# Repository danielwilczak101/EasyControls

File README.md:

# EasyControls Overview:

ADD IMAGE OF CUBESAT AND FREE FLIER

### [EasyControls.org](http://easycontrols.org)
The website is used to allow users to upload their controls code and see how the spacecraft responds.

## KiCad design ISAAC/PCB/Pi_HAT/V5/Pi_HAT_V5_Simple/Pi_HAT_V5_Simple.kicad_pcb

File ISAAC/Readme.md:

# ISAAC:

<p align="center"> 
  <kbd>
    
  </kbd>
</p>

Originally part of the NASA Asteroid flyer program has been repurposed by the EPPL to allow anyone interested in controls to go online and connect with a real working device and test their own control algorithms on a live device that is connected to the global internet. The spacecraft has been refitted with new and improved wiring, updated computers and a website that allows for members to connect and upload code to.

### [EasyControls.org](http://easycontrols.org)
The website is used to allow users to upload their controls code and see how the spacecraft responds.

**AsteroidFreeFlier original purpose:**  
https://www.nasa.gov/feature/extreme-access-flyer-to-take-planetary-exploration-airborne

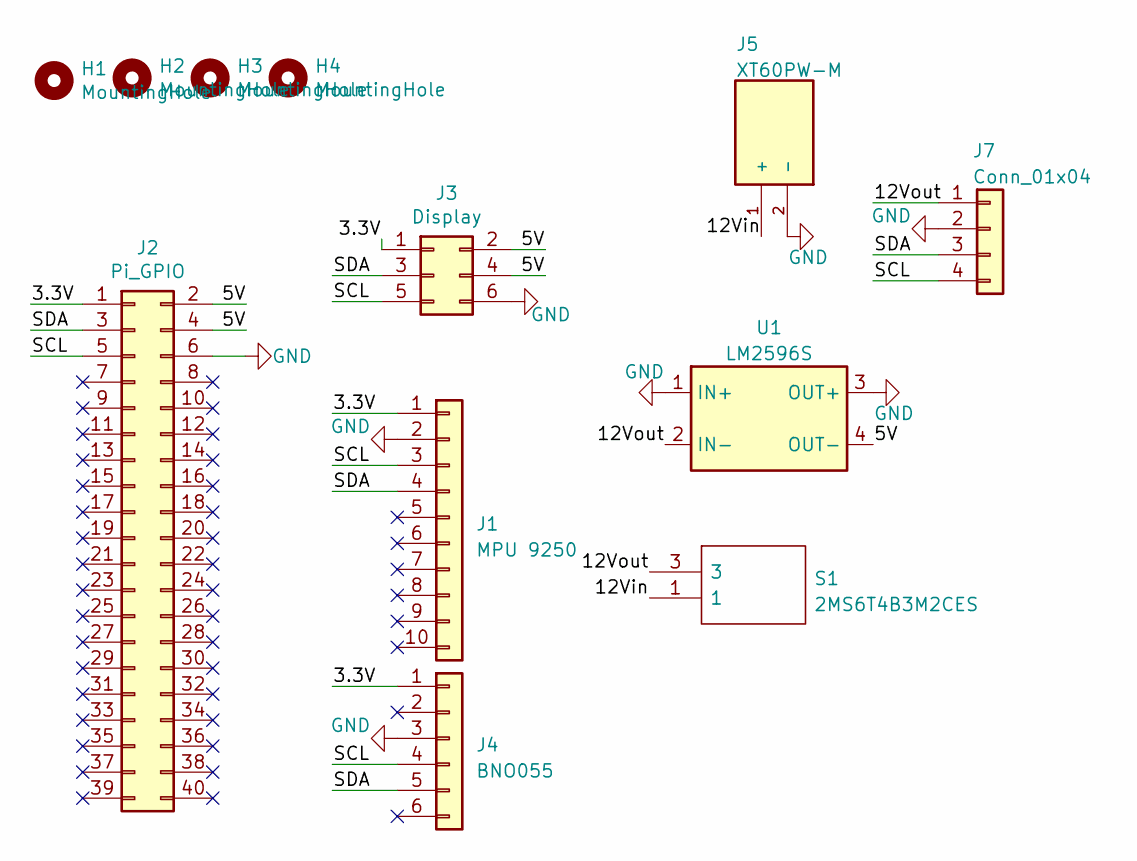
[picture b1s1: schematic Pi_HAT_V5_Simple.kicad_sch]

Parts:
H1, H2, H3, H4: MountingHole; MountingHole_2.5mm
J1: MPU 9250; PinHeader_1x10_P2.54mm_Vertical
J2: Pi_GPIO; PinHeader_2x20_P2.54mm_Vertical
J3: Display; PinHeader_2x03_P2.54mm_Vertical
J4: BNO055; PinHeader_1x06_P2.54mm_Vertical
J5: XT60PW-M; AMASS_XT60PW-M; PARTREV V1.2
J7: Conn_01x04; PinHeader_1x04_P2.54mm_Vertical
S1: 2MS6T4B3M2CES; Mouser Part Number 118-2MS6T4B3M2CES
U1: LM2596S; LM2596S_mod

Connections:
/3.3V: J1.1, J2.1, J3.1, J4.1
/5V: J2.2, J2.4, J3.2, J3.4, U1.4 (OUT-)
/12Vin: J5.1 (+), S1.1
/12Vout: J7.1, S1.3, U1.2 (IN-)
/SCL: J1.3, J2.5, J3.5, J4.4, J7.4
/SDA: J1.4, J2.3, J3.3, J4.5, J7.3
GND: J1.2, J2.6, J3.6, J4.3, J5.2 (-), J7.2, U1.1 (IN+), U1.3 (OUT+)

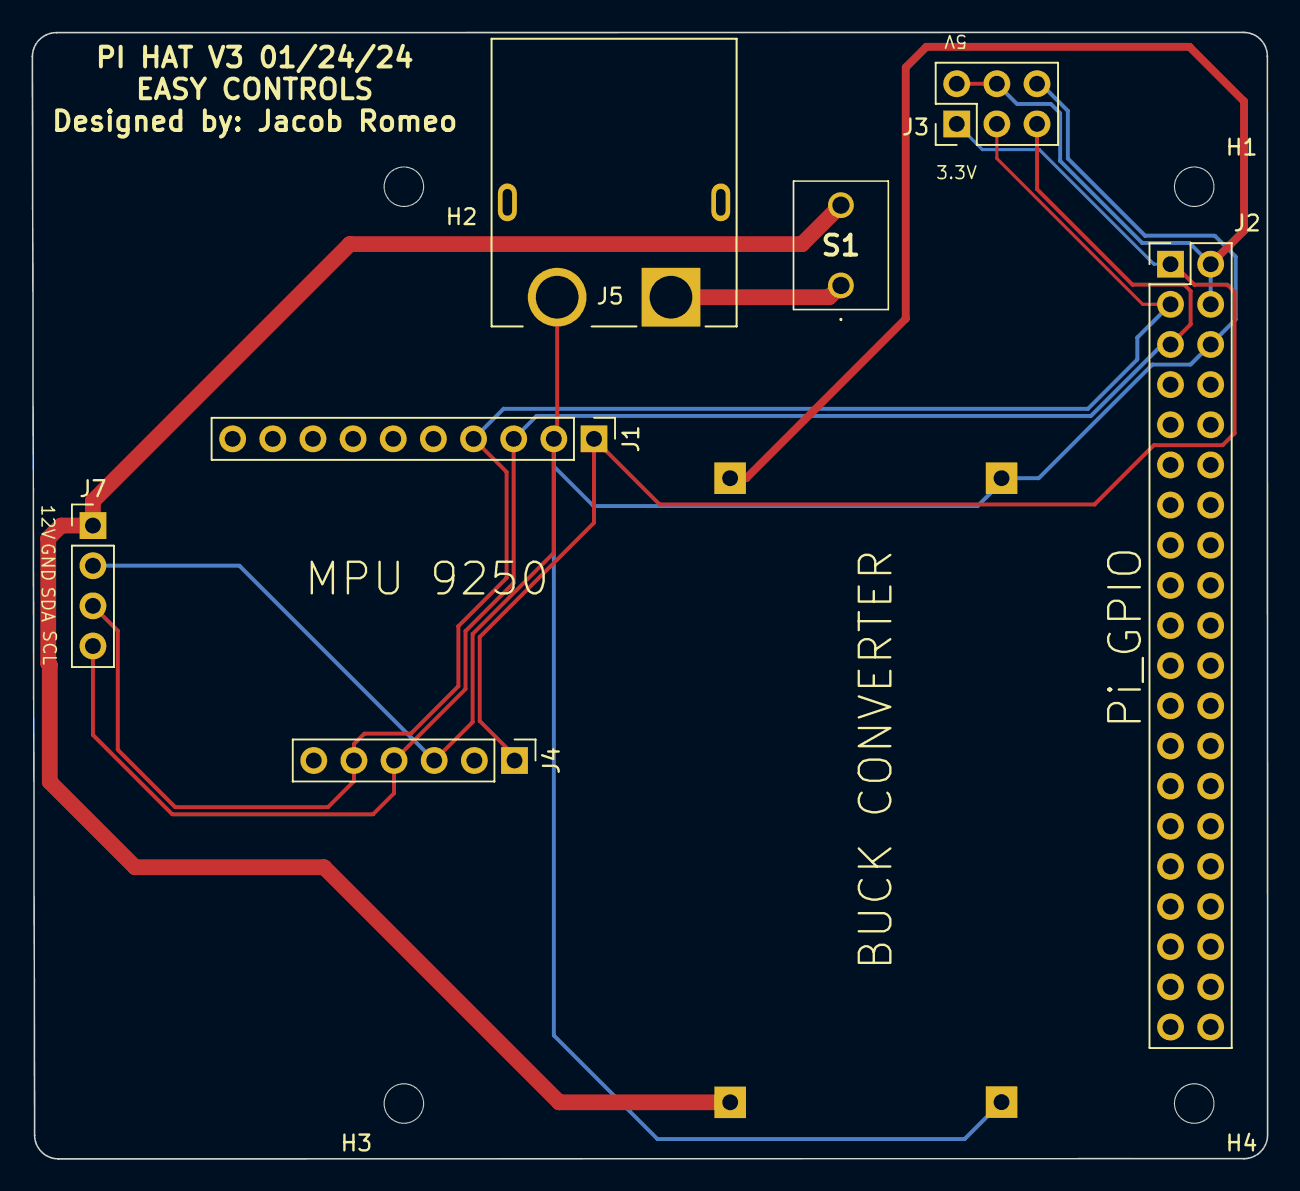
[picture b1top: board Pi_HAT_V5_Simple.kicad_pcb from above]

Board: 2 copper layers, 78.1 x 71.3 mm, 12 parts (1 on the bottom side), 7 nets.

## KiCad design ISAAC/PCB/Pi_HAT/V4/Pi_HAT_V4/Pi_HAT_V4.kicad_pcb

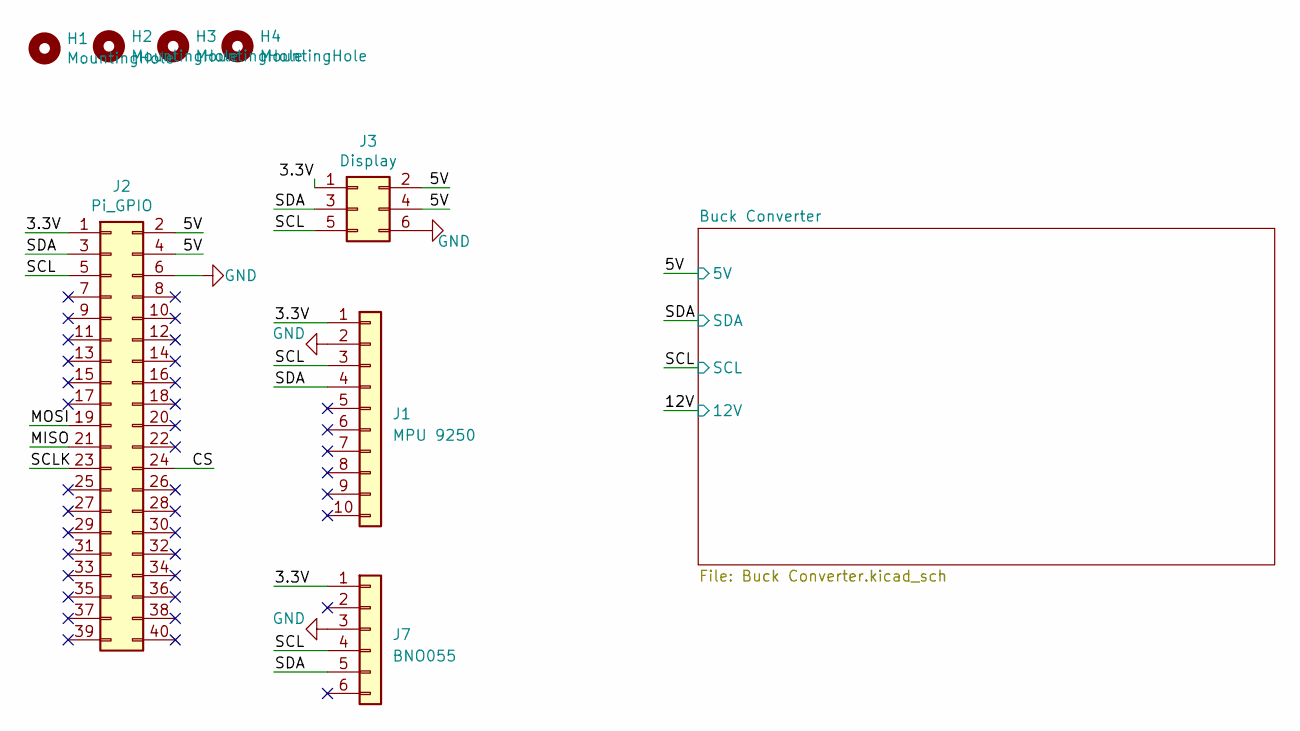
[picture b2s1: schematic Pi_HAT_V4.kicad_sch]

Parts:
H1, H2, H3, H4: MountingHole; MountingHole_2.5mm
J1: MPU 9250; PinHeader_1x10_P2.54mm_Vertical
J2: Pi_GPIO; PinHeader_2x20_P2.54mm_Vertical
J3: Display; PinHeader_2x03_P2.54mm_Vertical
J7: BNO055; PinHeader_1x06_P2.54mm_Vertical

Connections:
/3.3V: J1.1, J2.1, J3.1, J7.1
/5V: J2.2, J2.4, J3.2, J3.4; also elsewhere on the board
/CS: J2.24
/MISO: J2.21
/MOSI: J2.19
/SCL: J1.3, J2.5, J3.5, J7.4; also elsewhere on the board
/SCLK: J2.23
/SDA: J1.4, J2.3, J3.3, J7.5; also elsewhere on the board
GND: J1.2, J2.6, J3.6, J7.3; also elsewhere on the board

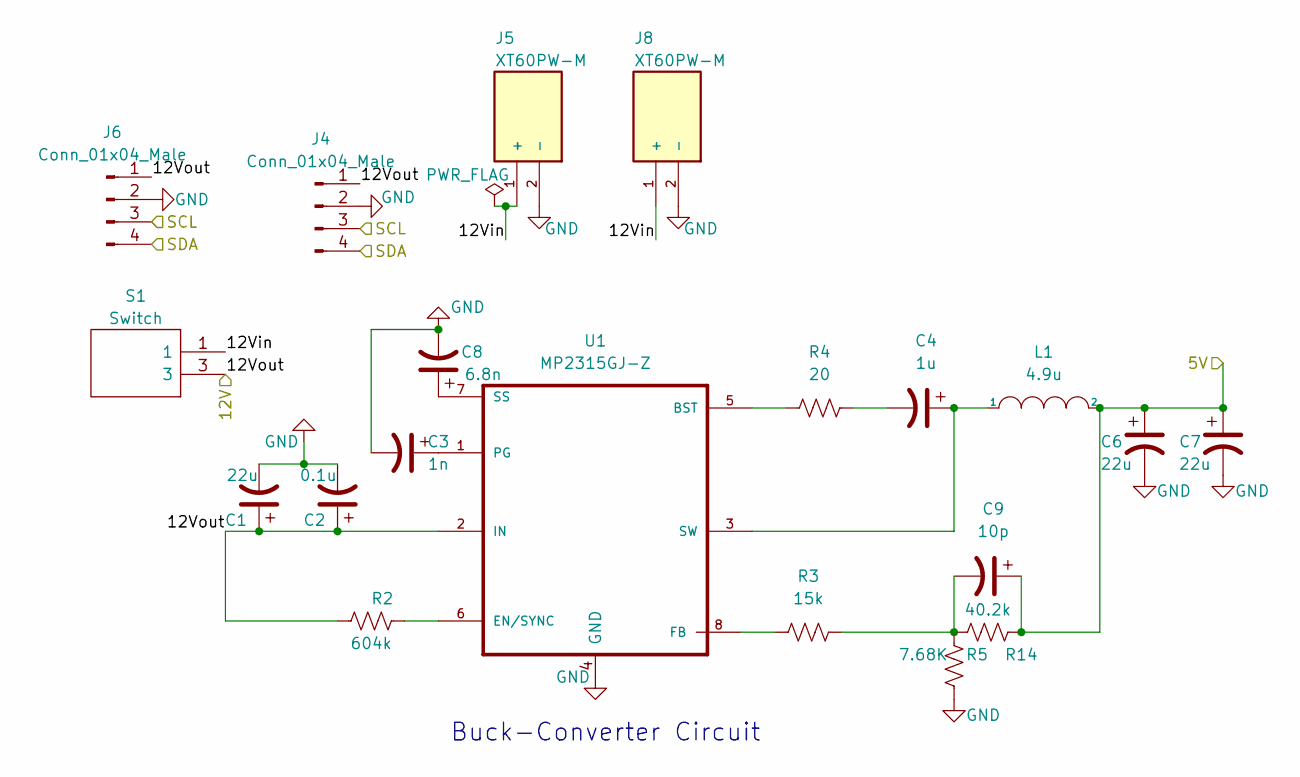
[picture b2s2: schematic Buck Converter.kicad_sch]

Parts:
C1, C6, C7: 22u; C_1210_3225Metric_Pad1.33x2.70mm_HandSolder
C2: 0.1u; C_1210_3225Metric_Pad1.33x2.70mm_HandSolder
C3: 1n; C_0603_1608Metric_Pad1.08x0.95mm_HandSolder
C4: 1u; C_0603_1608Metric_Pad1.08x0.95mm_HandSolder
C8: 6.8n; C_0603_1608Metric_Pad1.08x0.95mm_HandSolder
C9: 10p; C_0603_1608Metric_Pad1.08x0.95mm_HandSolder
J4, J6: Conn_01x04_Male; PinHeader_1x04_P2.54mm_Vertical
J5, J8: XT60PW-M; AMASS_XT60PW-M; PARTREV V1.2
L1: 4.9u; 744777004
R2: 604k; R_1206_3216Metric_Pad1.30x1.75mm_HandSolder
R3: 15k; R_0805_2012Metric_Pad1.20x1.40mm_HandSolder
R4: 20; R_0603_1608Metric_Pad0.98x0.95mm_HandSolder
R5: 7.68K; R_0805_2012Metric_Pad1.20x1.40mm_HandSolder
R14: 40.2k; R_0805_2012Metric_Pad1.20x1.40mm_HandSolder
S1: Switch; 2MS6T4B3M2CES; Mouser Part Number 118-2MS6T4B3M2CES
U1: MP2315GJ-Z; MP2393GTL-P

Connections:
/5V: C6.1, C7.1, C9.1, L1.2, R14.1; also elsewhere on the board
/12V: C1.1, C2.1, J4.1, J6.1, R2.1, S1.3, U1.2 (IN)
/Buck Converter/12Vin: J5.1 (+), J8.1 (+), S1.1
/SCL: J4.3, J6.3; also elsewhere on the board
/SDA: J4.4, J6.4; also elsewhere on the board
GND: C1.2, C2.2, C3.2, C6.2, C7.2, C8.2, J4.2, J5.2 (-), J6.2, J8.2 (-), R5.1, U1.4 (GND); also elsewhere on the board
unnamed: C4.2, R4.2
unnamed: C9.2, R3.2, R5.2, R14.2
unnamed: R4.1, U1.5 (BST)
unnamed: R2.2, U1.6 (EN/SYNC)
unnamed: R3.1, U1.8 (FB)
unnamed: C3.1, U1.1 (PG)
unnamed: C8.1, U1.7 (SS)
unnamed: C4.1, L1.1, U1.3 (SW)

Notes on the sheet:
Buck-Converter Circuit

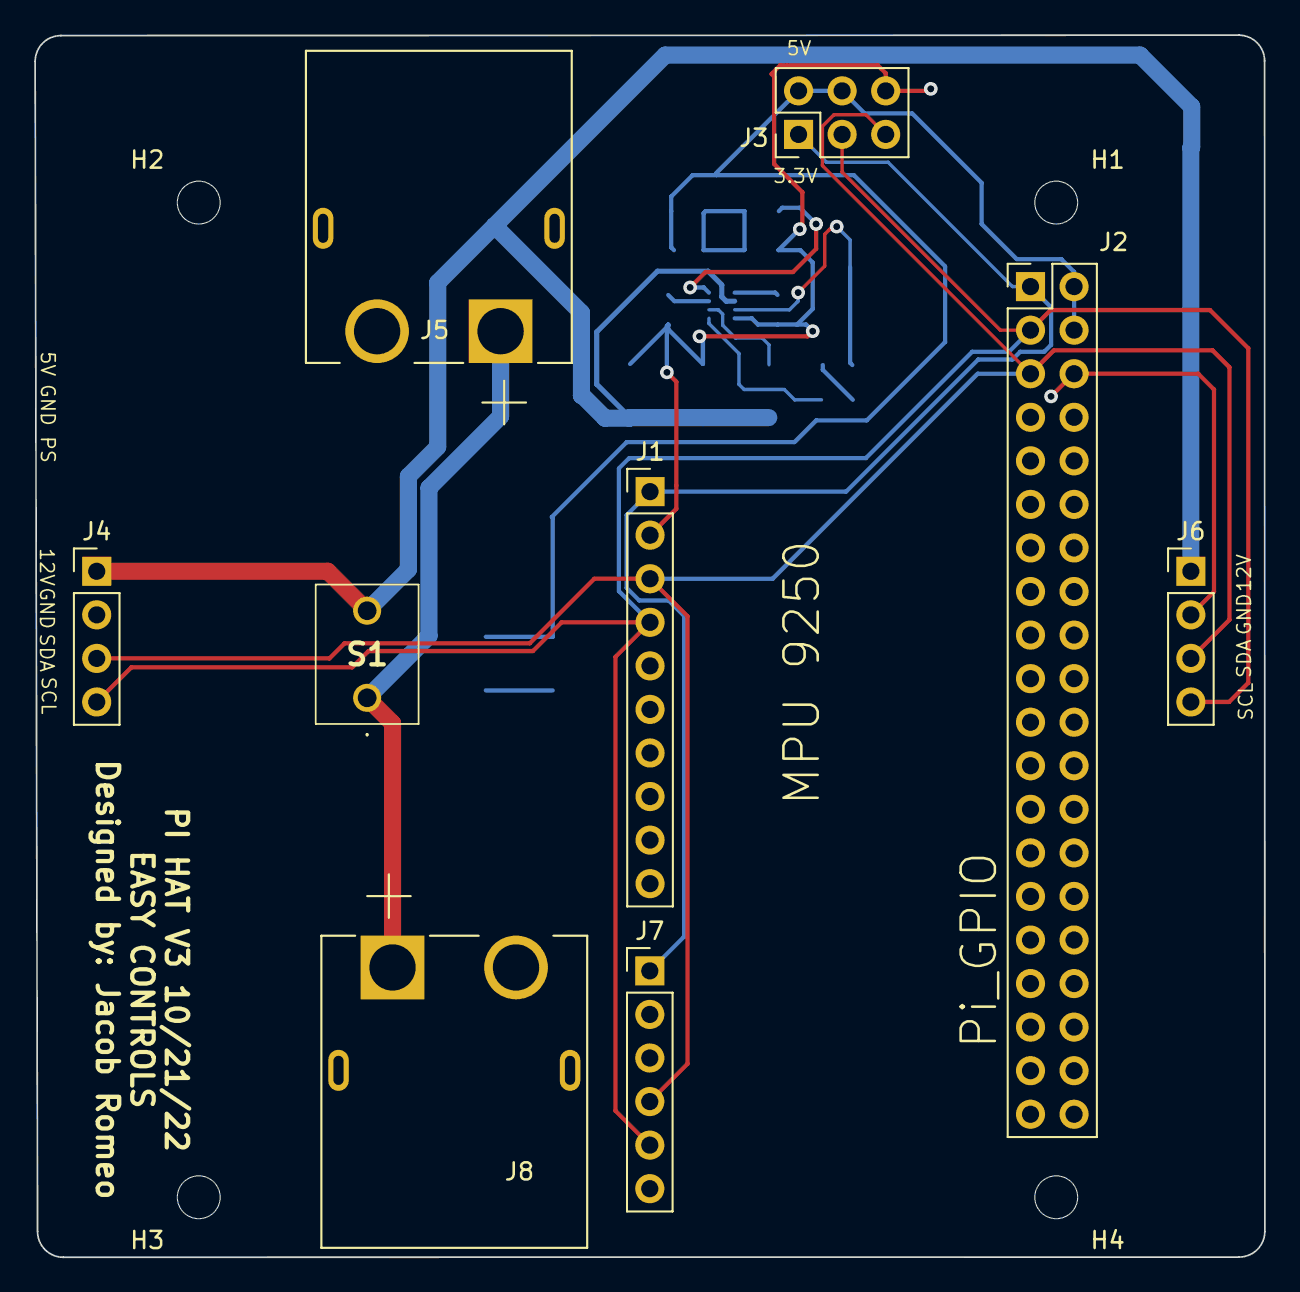
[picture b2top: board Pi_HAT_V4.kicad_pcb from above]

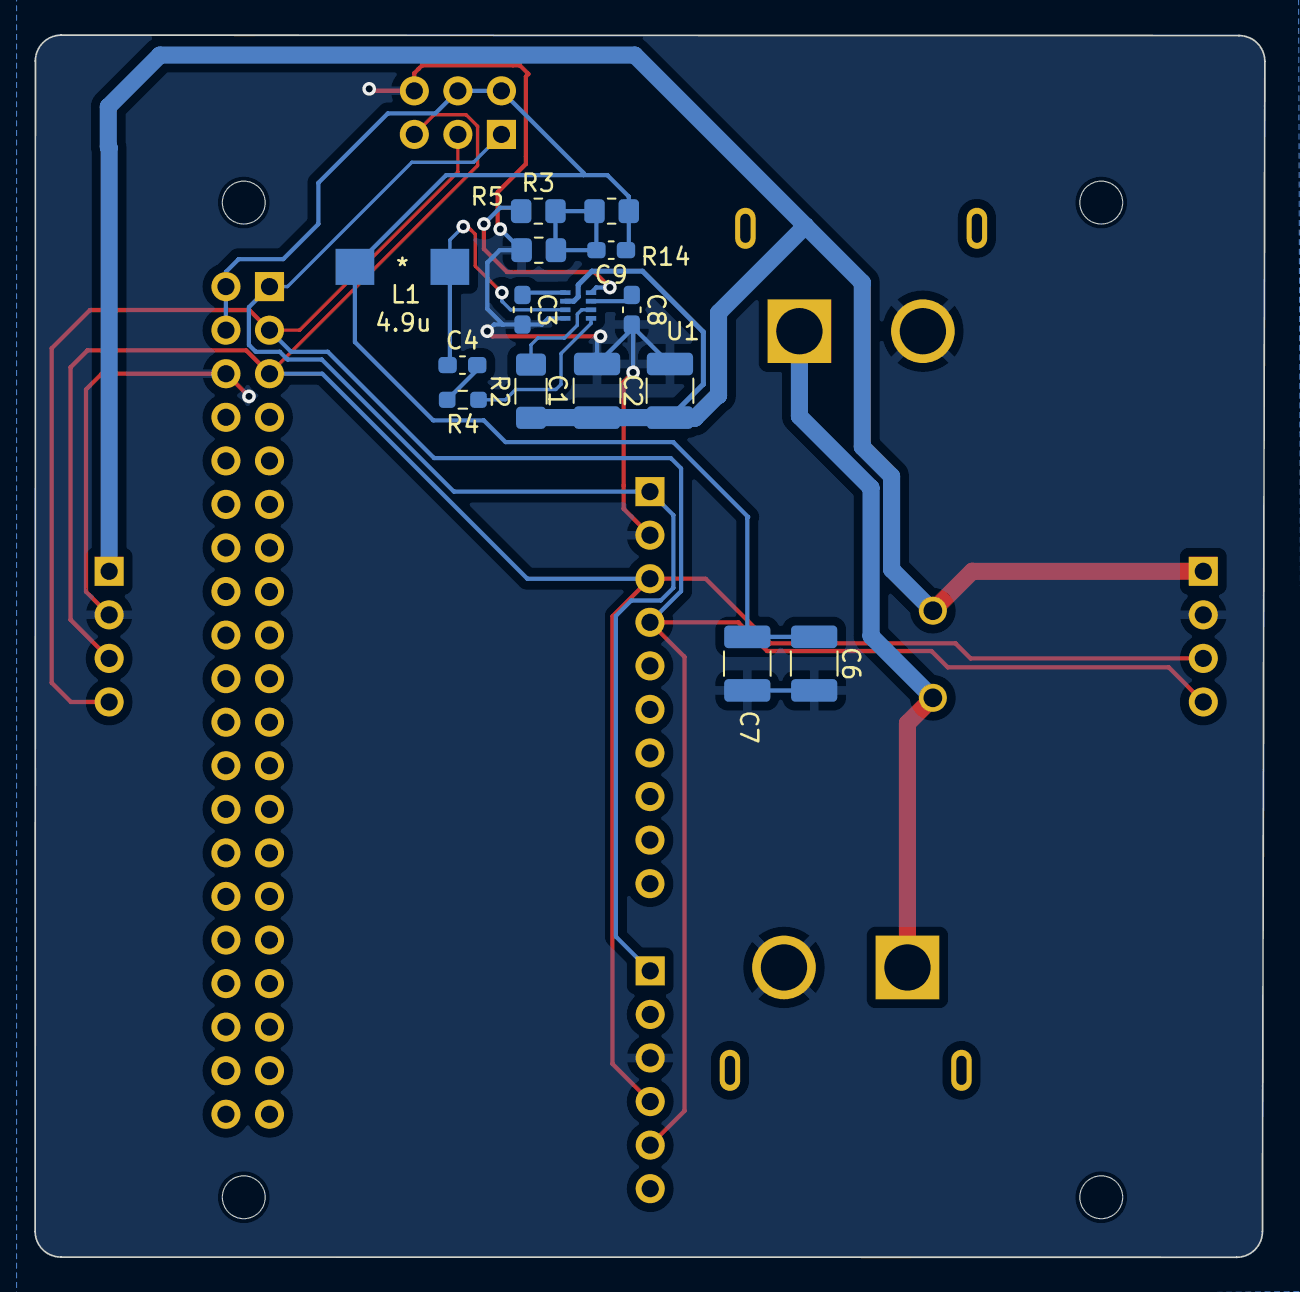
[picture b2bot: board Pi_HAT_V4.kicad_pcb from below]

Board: 2 copper layers, 71.7 x 71.3 mm, 28 parts (15 on the bottom side), 15 nets.

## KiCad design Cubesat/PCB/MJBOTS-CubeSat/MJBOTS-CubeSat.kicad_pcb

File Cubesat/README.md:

# Adafruit MPU6050 Tutorial

## Pin Setup
![Imagine of Wiring Connections](https://ci3.googleusercontent.com/mail-img-att/AFCqZUThCiJzJdf5VEPteI38iU4qnCil-Sh8_i3cN5V2-CpUgZl--BT6T41QAQx5CnERvZO2G-tCWW8L4dy0hpVCbDTkbaTJOeb_-uVqiqYysCVO6LnAdNoPUOyvBJOToGWDmonSgrcMjQwpos4TAGAm7Wb2Y2q7FP-hSKtcxXmohh_ocbb2QgcuV42Qs1p731DiRPBw8EQ1PGIHDRJtui4Eidqv2VdiTuQr0OY7wOFFXi9l2X-p-xWPghV6yXjCQQFoPtGQH4euV5N5c4-ckY_soG8GE949CwQs3TM7Esc5M0UYe7IHWo136j9-g-rpMt5ZEcD7Y1NYwC7rCI46KGSFGiejAC2qMYsi3DFWj7SGz_AVnYmfNsXVhE0isgnpOYCD6Rc_9uzAtjNlQr5A-Q1i58PURXv468tTernak52G0SzaolKX8-qcxqE_hWZ8D8fjc39rNlD6i9PonuLUA1Lji4xH6IpdAkDVgAl7JYSdlAL-qM81bYAi-k9IxM4VFPfifPQYRhF95_F9B4Ep7n9SIFkirArgT5kmE9S___ffsfuOm7T7rsrR3v_TzfFf-P9-775C06vVTxAHMhT1TpJlYycQEYDWsajXwu2Ka95v7_fh1Z8Ta2ciBfkmPyyqYoDWGuBV6eTWnhS-9je5aY975QFgwUleCTfClFN8wjRZngjrZI4lxD3py9Uyd2Latz6-hG2I44vT3fwgiN2kLwgbf4zWOMhUGlvRW9hSuI7epzOKFeJ3jODHBQjJbCPp2q_a8-IquQ2PJsLU9ZGftmnfUyDumi8GQgjkkXITWcaJcmDB8TyMsOwDnfZYYmvHOFacr18GFflIZVdb46hrCQZr8WKl1NOrC4IHyXKK9du6CoEw2tTaT9JWCO56K9zZPJlxBnxJfAGzqpIz4qywLsoLMYroEC6exl34u24X5ZThnvgWI3Y2n-cJurGJUFWdHnlcmcaQMpdaAbdeg9_peH106gJGLmObRJf1PD6m=s0-l75-ft)

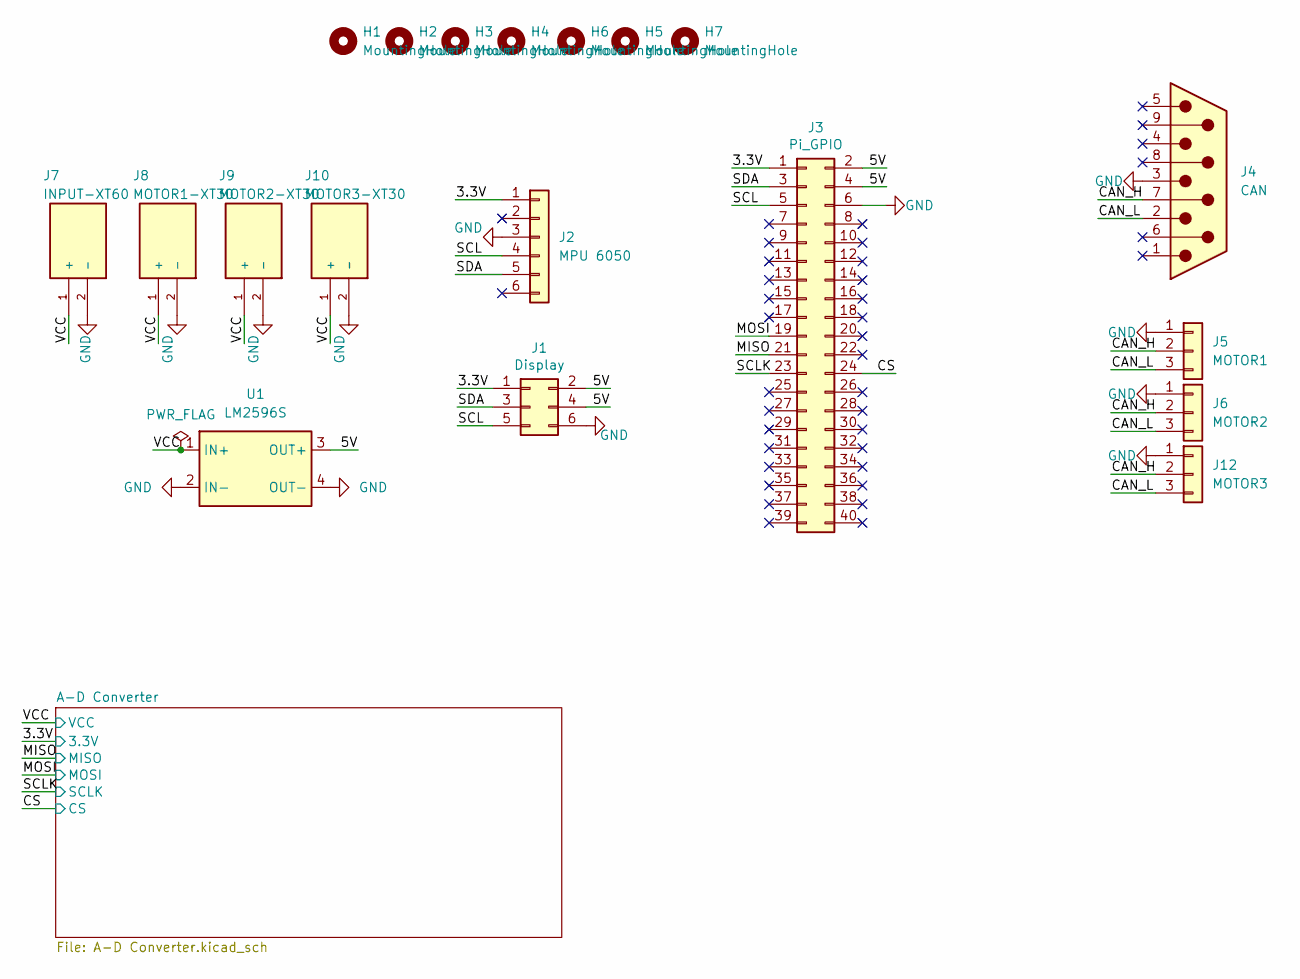
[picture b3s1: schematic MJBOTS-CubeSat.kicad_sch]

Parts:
H1, H2, H3, H4, H5, H6, H7: MountingHole; MountingHole_2.5mm
J1: Display; PinHeader_2x03_P2.54mm_Vertical
J2: MPU 6050; PinHeader_1x06_P2.54mm_Vertical
J3: Pi_GPIO; PinHeader_2x20_P2.54mm_Vertical
J4: CAN; DSUB-9_Male_Vertical_P2.77x2.84mm
J5: MOTOR1; PinHeader_1x03_P2.54mm_Vertical
J6: MOTOR2; PinHeader_1x03_P2.54mm_Vertical
J7: INPUT-XT60; AMASS_XT60PW-M; PARTREV V1.2
J8: MOTOR1-XT30; XT30PWM; PARTREV V1.2
J9: MOTOR2-XT30; XT30PWM; PARTREV V1.2
J10: MOTOR3-XT30; XT30PWM; PARTREV V1.2
J12: MOTOR3; PinHeader_1x03_P2.54mm_Vertical
U1: LM2596S; LM2596S_mod

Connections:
/3.3V: J1.1, J2.1, J3.1; also elsewhere on the board
/5V: J1.2, J1.4, J3.2, J3.4, U1.3 (OUT+)
/CAN_H: J4.7, J5.2, J6.2, J12.2
/CAN_L: J4.2, J5.3, J6.3, J12.3
/CS: J3.24; also elsewhere on the board
/MISO: J3.21; also elsewhere on the board
/MOSI: J3.19; also elsewhere on the board
/SCL: J1.5, J2.4, J3.5
/SCLK: J3.23; also elsewhere on the board
/SDA: J1.3, J2.5, J3.3
/VCC: J7.1 (+), J8.1 (+), J9.1 (+), J10.1 (+), U1.1 (IN+); also elsewhere on the board
GND: J1.6, J2.3, J3.6, J4.3, J5.1, J6.1, J7.2 (-), J8.2 (-), J9.2 (-), J10.2 (-), J12.1, U1.2 (IN-), U1.4 (OUT-); also elsewhere on the board

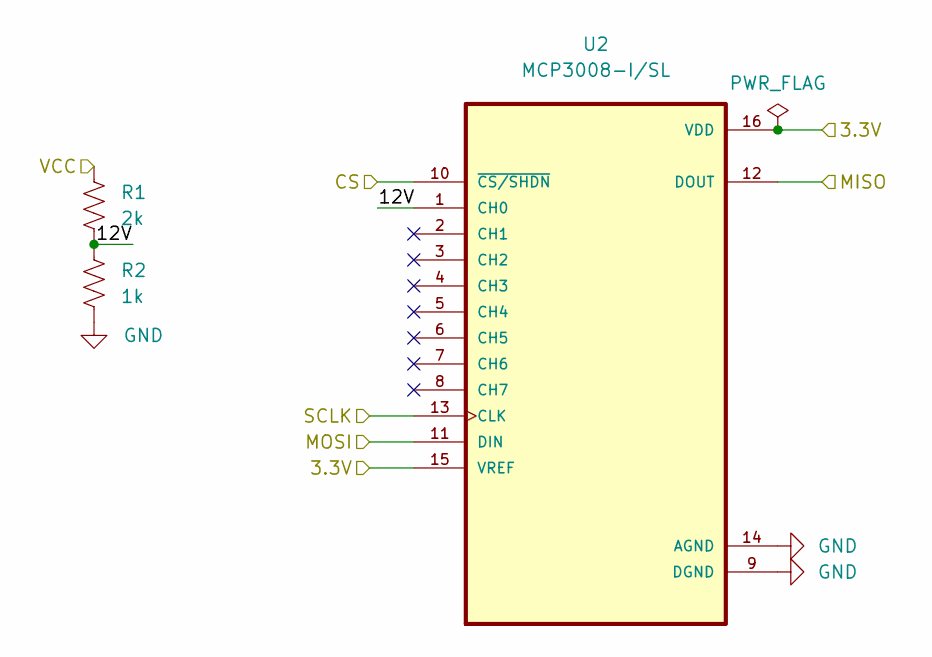
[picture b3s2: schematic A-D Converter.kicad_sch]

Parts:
R1: 2k; R_0805_2012Metric_Pad1.20x1.40mm_HandSolder
R2: 1k; R_0805_2012Metric_Pad1.20x1.40mm_HandSolder
U2: MCP3008-I/SL; SOIC127P600X175-16N

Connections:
/3.3V: U2.15 (VREF), U2.16 (VDD); also elsewhere on the board
/A-D Converter/12V: R1.1, R2.1, U2.1 (CH0)
/CS: U2.10 (~CS/SHDN); also elsewhere on the board
/MISO: U2.12 (DOUT); also elsewhere on the board
/MOSI: U2.11 (DIN); also elsewhere on the board
/SCLK: U2.13 (CLK); also elsewhere on the board
/VCC: R1.2; also elsewhere on the board
GND: R2.2, U2.9 (DGND), U2.14 (AGND); also elsewhere on the board

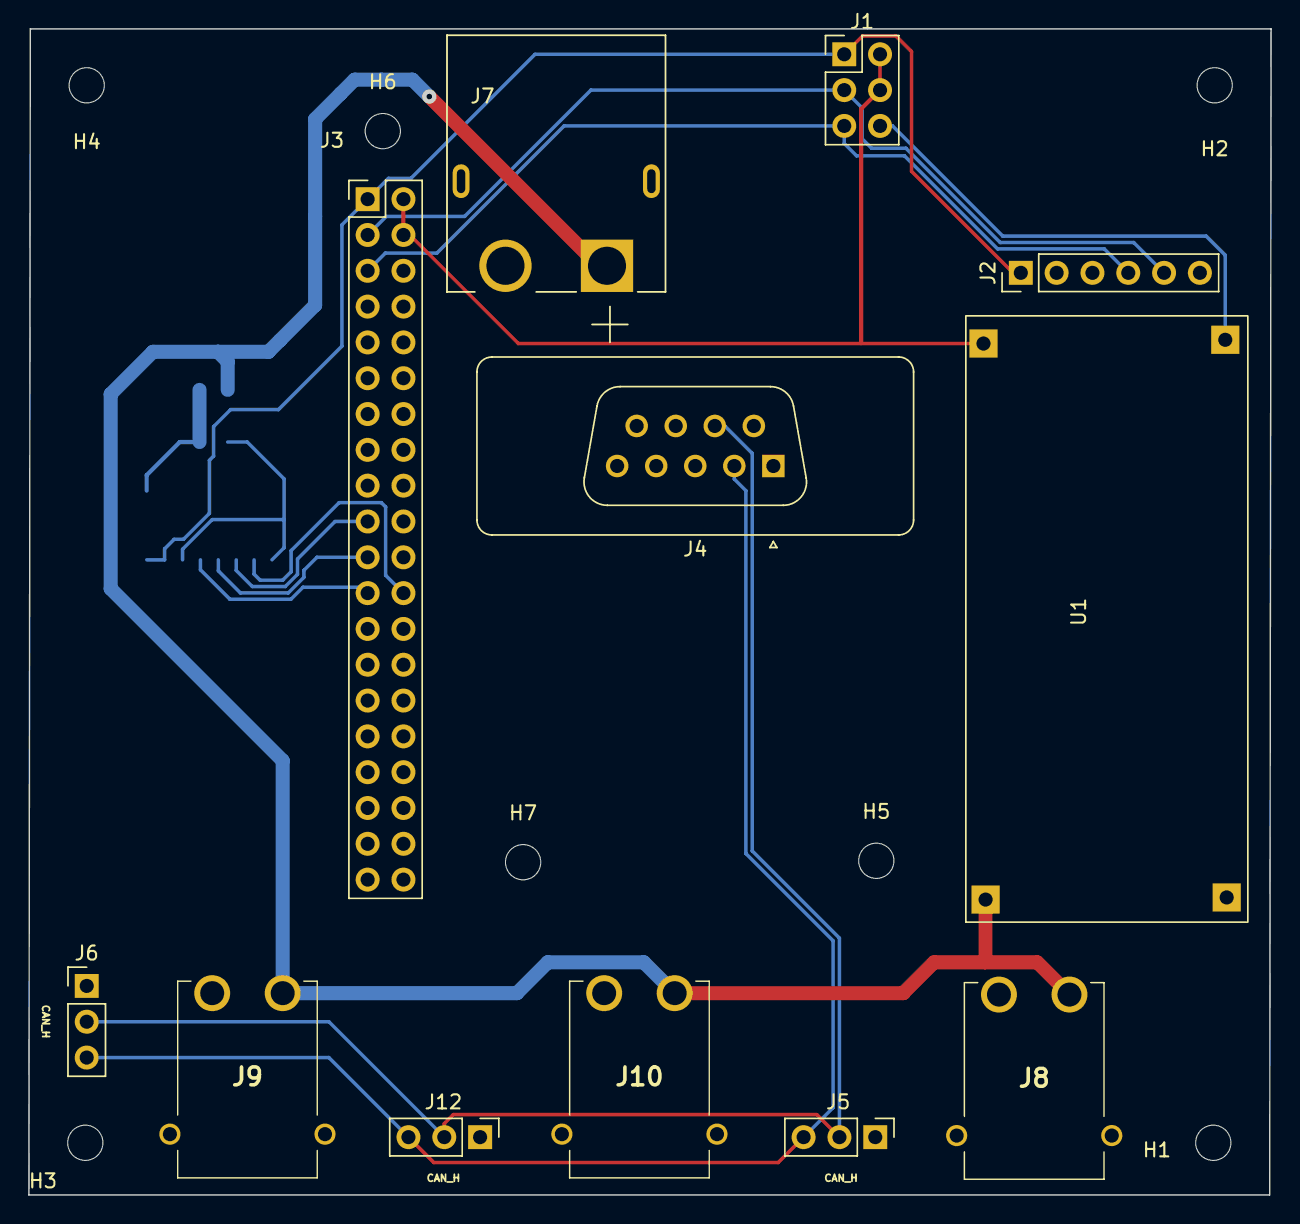
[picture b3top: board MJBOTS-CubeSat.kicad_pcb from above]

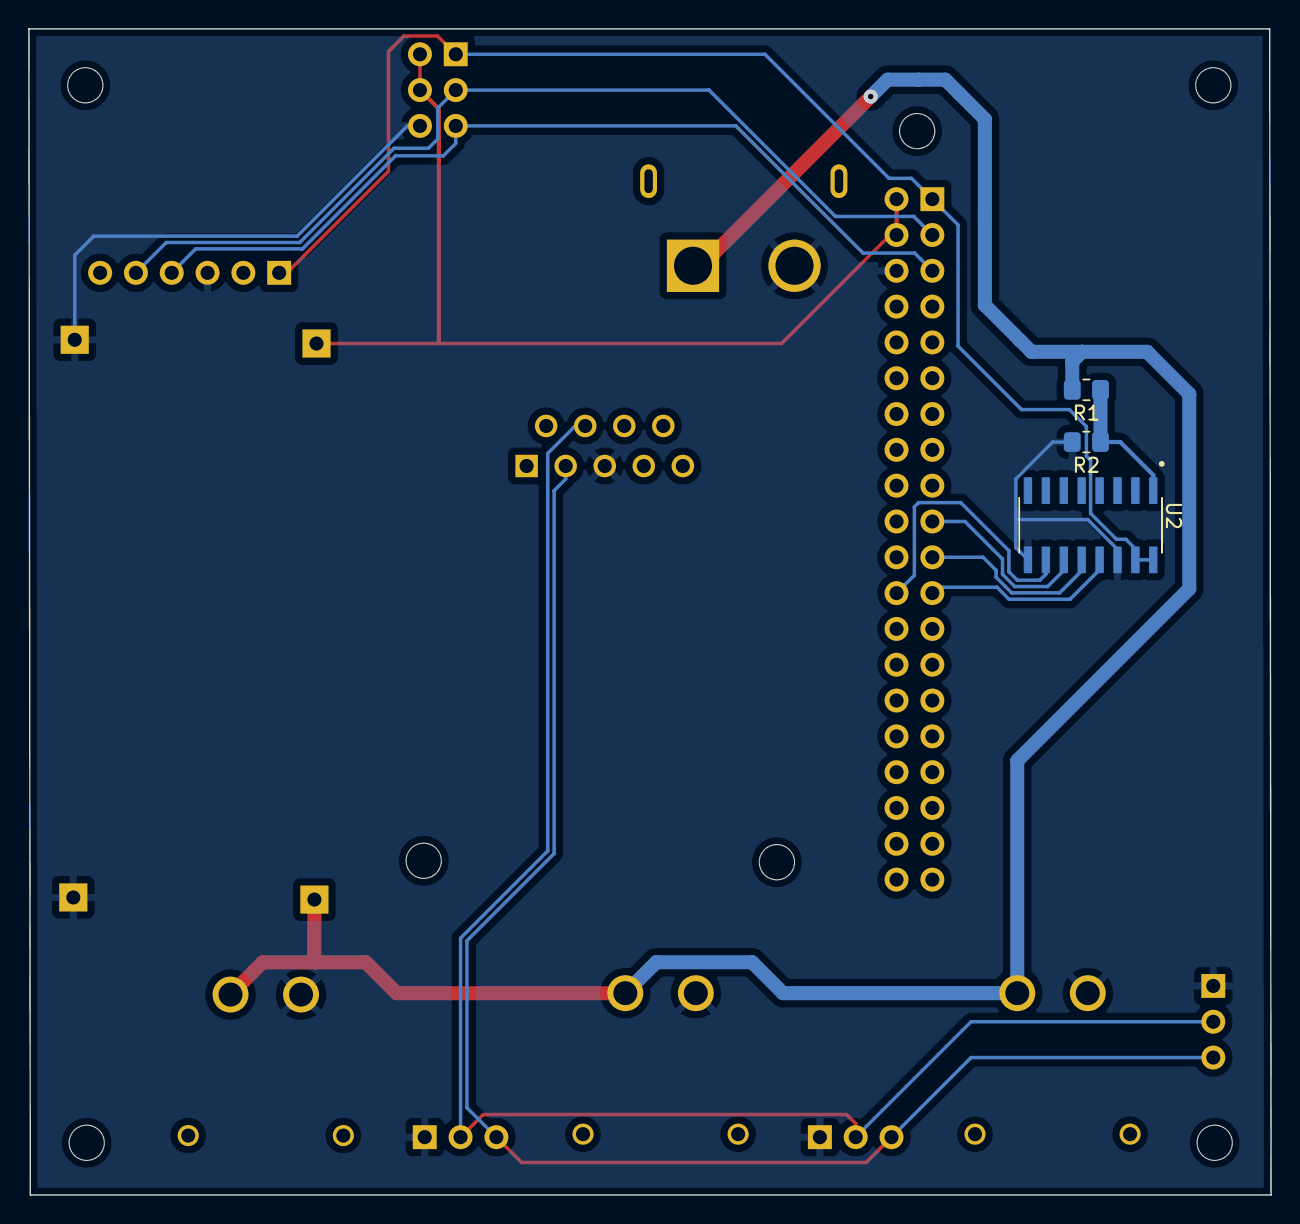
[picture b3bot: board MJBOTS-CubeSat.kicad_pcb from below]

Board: 2 copper layers, 88.1 x 82.7 mm, 22 parts (3 on the bottom side), 13 nets.

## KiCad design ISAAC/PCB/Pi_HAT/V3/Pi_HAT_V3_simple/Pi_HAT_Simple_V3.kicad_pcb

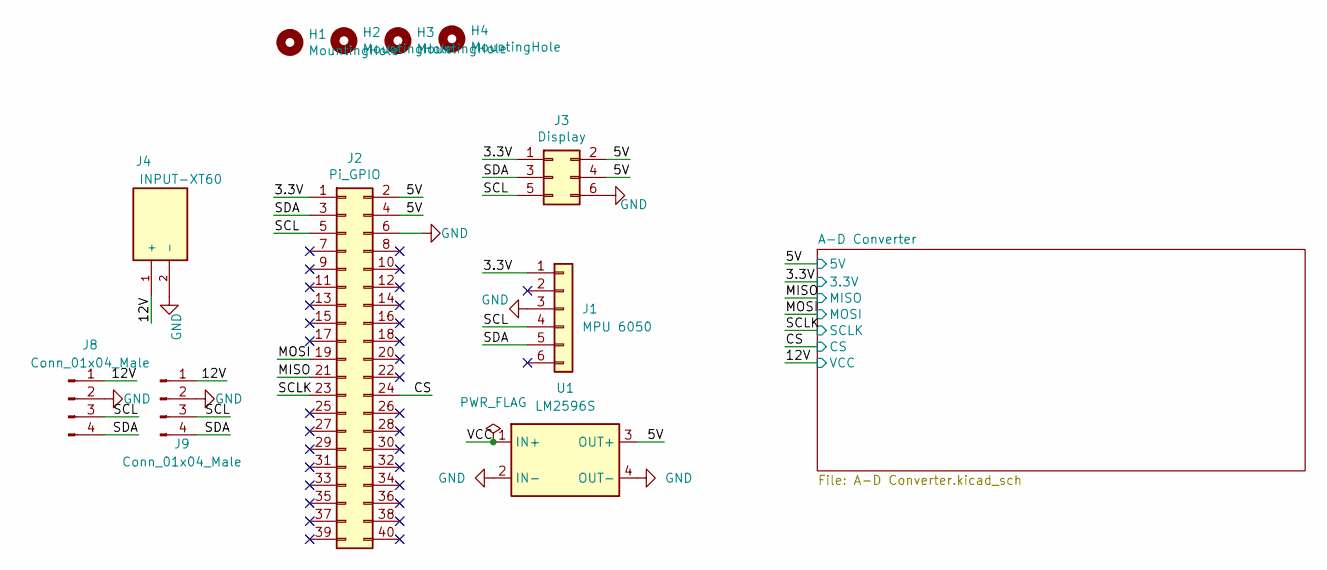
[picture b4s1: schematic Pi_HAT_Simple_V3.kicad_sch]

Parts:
H1, H2, H3, H4: MountingHole; MountingHole_2.5mm
J1: MPU 6050; PinHeader_1x06_P2.54mm_Vertical
J2: Pi_GPIO; PinHeader_2x20_P2.54mm_Vertical
J3: Display; PinHeader_2x03_P2.54mm_Vertical
J4: INPUT-XT60; AMASS_XT60PW-M; PARTREV V1.2
J8, J9: Conn_01x04_Male; PinHeader_1x04_P2.54mm_Vertical
U1: LM2596S; LM2596S_mod

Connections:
/3.3V: J1.1, J2.1, J3.1; also elsewhere on the board
/5V: J2.2, J2.4, J3.2, J3.4, U1.3 (OUT+); also elsewhere on the board
/12V: J4.1 (+), J8.1, J9.1; also elsewhere on the board
/CS: J2.24; also elsewhere on the board
/MISO: J2.21; also elsewhere on the board
/MOSI: J2.19; also elsewhere on the board
/SCL: J1.4, J2.5, J3.5, J8.3, J9.3
/SCLK: J2.23; also elsewhere on the board
/SDA: J1.5, J2.3, J3.3, J8.4, J9.4
/VCC: U1.1 (IN+)
GND: J1.3, J2.6, J3.6, J4.2 (-), J8.2, J9.2, U1.2 (IN-), U1.4 (OUT-); also elsewhere on the board

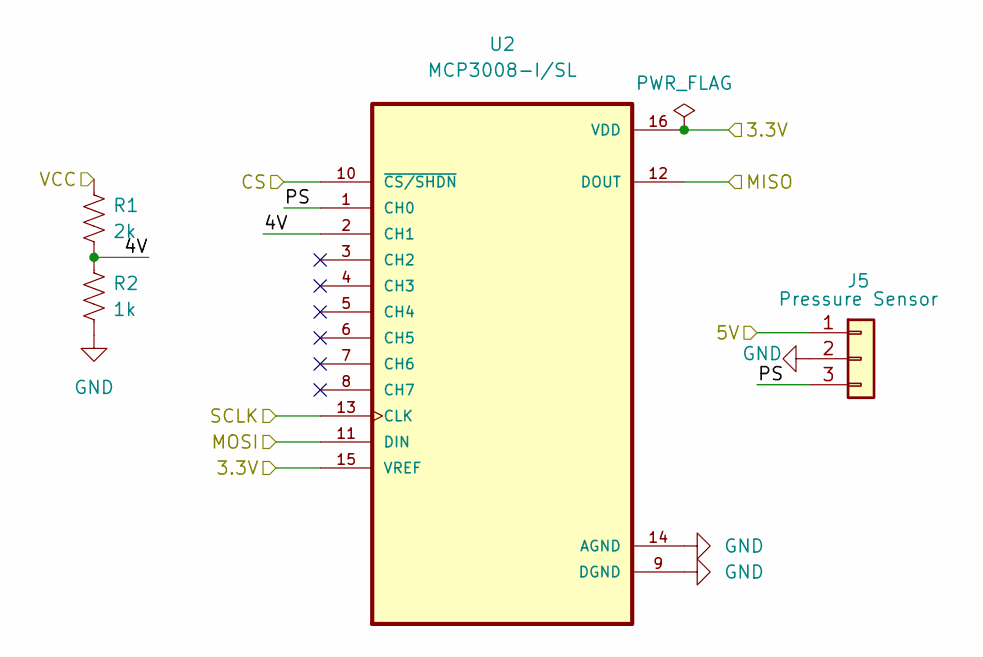
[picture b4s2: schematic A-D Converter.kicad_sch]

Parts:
J5: Pressure Sensor; PinHeader_1x03_P2.54mm_Vertical
R1: 2k; R_0805_2012Metric_Pad1.20x1.40mm_HandSolder
R2: 1k; R_0805_2012Metric_Pad1.20x1.40mm_HandSolder
U2: MCP3008-I/SL; SOIC127P600X175-16N

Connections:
/3.3V: U2.15 (VREF), U2.16 (VDD); also elsewhere on the board
/5V: J5.1; also elsewhere on the board
/12V: R1.1; also elsewhere on the board
/A-D Converter/4V: R1.2, R2.1, U2.2 (CH1)
/A-D Converter/PS: J5.3, U2.1 (CH0)
/CS: U2.10 (~CS/SHDN); also elsewhere on the board
/MISO: U2.12 (DOUT); also elsewhere on the board
/MOSI: U2.11 (DIN); also elsewhere on the board
/SCLK: U2.13 (CLK); also elsewhere on the board
GND: J5.2, R2.2, U2.9 (DGND), U2.14 (AGND); also elsewhere on the board

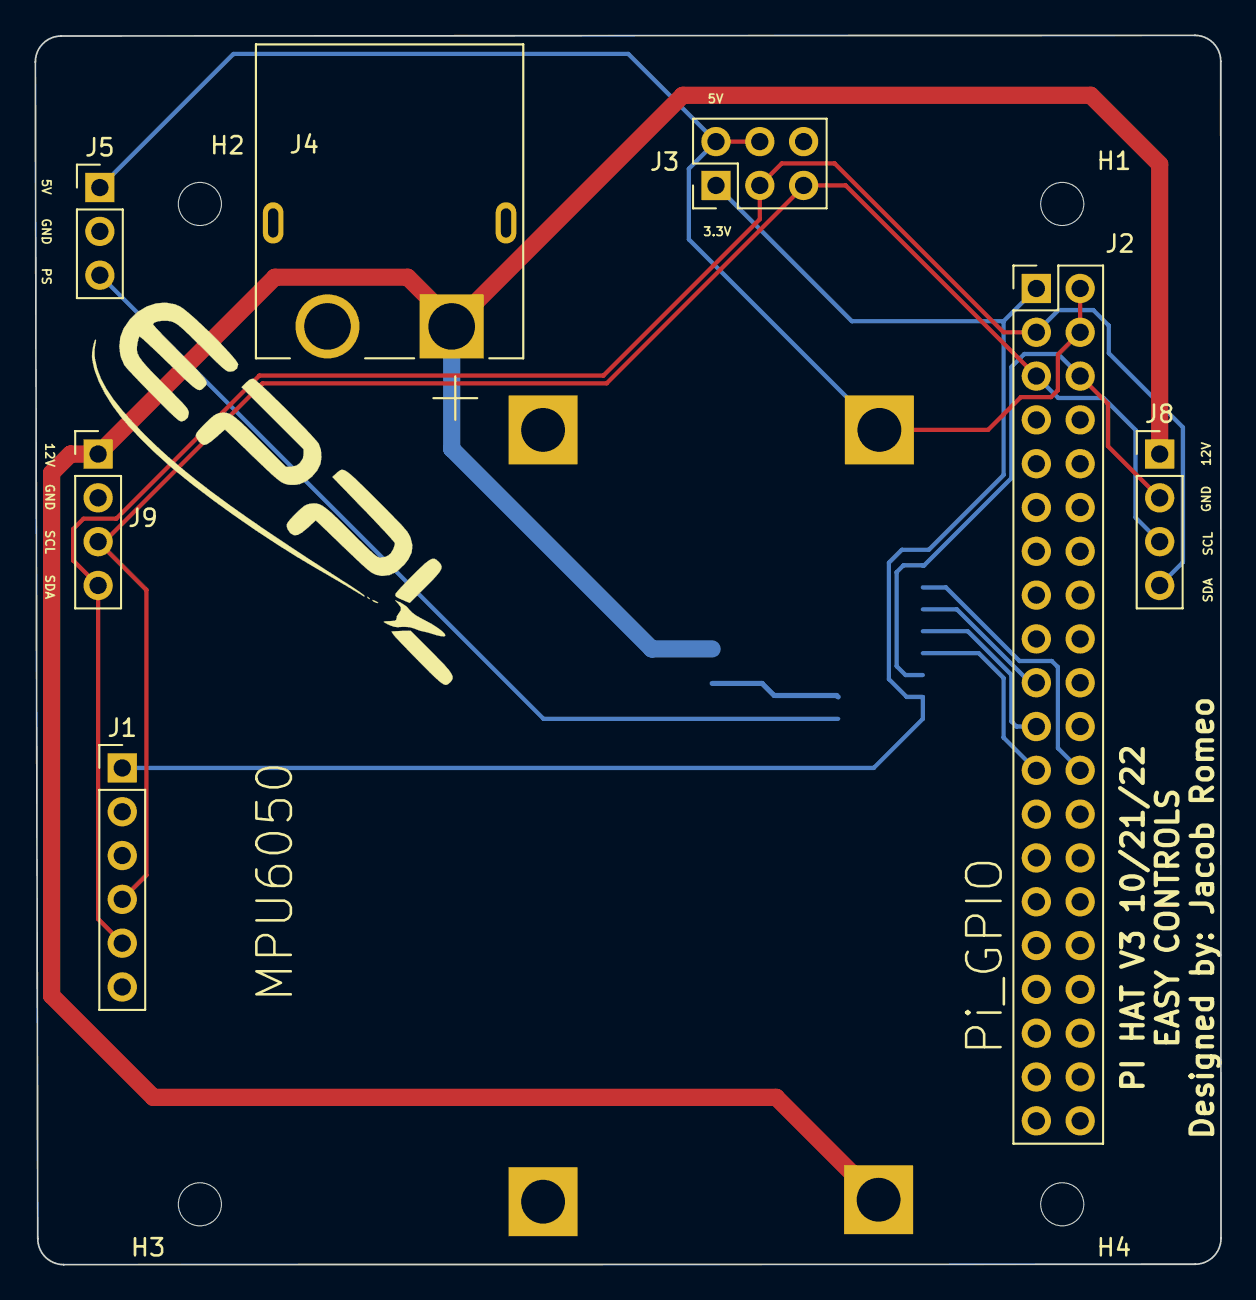
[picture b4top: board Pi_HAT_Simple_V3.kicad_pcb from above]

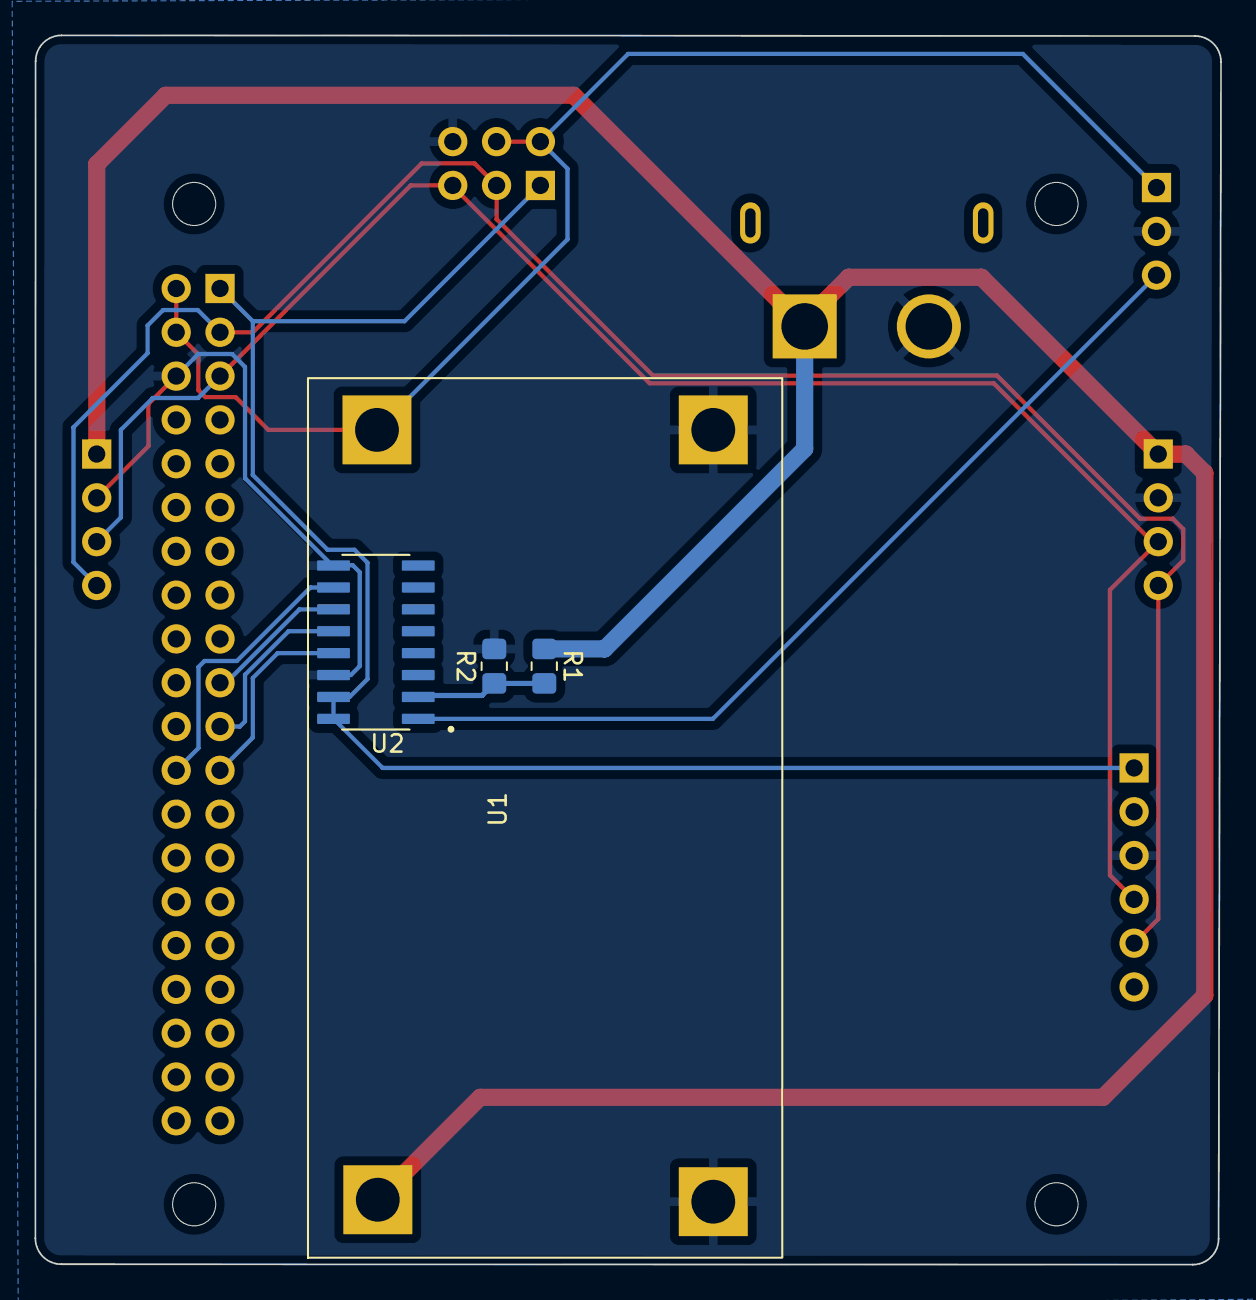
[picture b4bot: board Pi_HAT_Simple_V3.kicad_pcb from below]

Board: 2 copper layers, 68.7 x 71.3 mm, 15 parts (4 on the bottom side), 12 nets.

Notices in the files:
parts and their libraries:
Copyright 2021 Accelerated Designs. All rights reserved.
